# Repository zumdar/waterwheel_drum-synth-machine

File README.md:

# The Wacky Waterwheel Wonder Machine!

A synthesizer, drum machine, electromechanical, waterwheel powered musical intsrument!

.jpg>)

Started in Oct. 2022 in Nashville, TN as part of The Paradise Driveway residency, full working version complete in Oct. 2025.

Project created in collaboration with

- [Neil Fridd (aka Terror Pigeon)](https://terrorpigeon.bandcamp.com/)
- [Jen Gavin (aka Paradise MIDI)](https://paradisemidi.com/)

# Overview

The Waterwheel Wondermachine is a nature powered mechanical-electronic logic idea workstation. It is a hybrid of bass synthesizer, drum machine, and kinetic motor instrument. When it rains, the waterwheel spins and every spoke of the wheel triggers the machine to advance one step of the sequence.

It has the feel of an old analog switch board or the cockpit of an airplane with 50+ toggle switches, patch cables, and LEDs scattered everywhere. Intimidating as it may look from the outside — and even more so on the inside since the front panels are translucent — the machine is simple enough where anyone can walk up and play it!

When it rains, the machine generates evolving musical sequences mixed with the percussive sounds of the external motors striking parts of the frame. When the sun returns, it transforms into a contemplative sound sculpture, droning notes played on the touch canvas panel.

You can play a melody on the waterwheel drawing, using its cleverly arranged key sequence to inspire a new variation on the original idea. All of this is contingent on the correct environmental conditions (rain), so that you have a consistent performance. The rain sounds also play a sonic role, incorporating into the spacial ambiance.

# Tech Specs

- 16 step bass synthesizer sequencer
- 8 step, 4 sample drum sequencer
- 2x motor outputs, motors mounted in the instrument area, creating sounds by clever mounting with the motors hitting parts of the frame.
- All timing and sequencing done with CD4xxx logic chips and digital circuity, a complex puzzle of logic chips, inputs and outputs and buffering.
- the note input of the synthesizer is a drawing of a waterwheel and tree house (homage to Neil s backyard). We cut these pieces out of metal and are using capacitive touch to send those notes to the synthesizer.
- 1 big sample button to trigger a sample whenever the performer wants

# PCB

## V1 - etched

- Schematic was designed in October 2022. A PCB (well 3 actually...) were designed and then etched on the driveway on copper clad FR4 board. Here is the design:

- The etched PCB was tested and then a full PCB was designed and fabricated by JLCPCB

## V2 - fabricated PCB

[Link to Schematic for V2](https://github.com/zumdar/waterwheel_drum-synth-machine/blob/main/PCB/pcb_files_v2%20-%20fabricated%20PCB/waterwhel_V2_SCHEMATIC.pdf)

## PCB V2 errors

- no pulldown for clock
- 555 footprint doesnt fit
- some silkscreen labels are covered up by connectors

# References

[getting trigger from sequencer - casper electronics ](https://web.archive.org/web/20130509102109/http://casperelectronics.com/2007/03/19/sequencer-update/)

[more info about multi channel 4017 sequencer/trigger - sailor mouth](https://web.archive.org/web/20160915053601/http://www.sailormouth.org/trigseq2.html)

[how to get a easy trigger with the 4017 sequecner - little gate seq - electro music forum](https://electro-music.com/forum/topic-63020.html)

[MFOS 4017 sequencer lots of good info on how it works](http://musicfromouterspace.com/analogsynth_new/TENSTEPSEQUENCER/TENSTEPSEQUENCER.php)

[classic baby 10 sequencer](https://hackaday.com/2016/01/14/oh-baby-baby10-build-a-classic-analog-music-sequencer/)

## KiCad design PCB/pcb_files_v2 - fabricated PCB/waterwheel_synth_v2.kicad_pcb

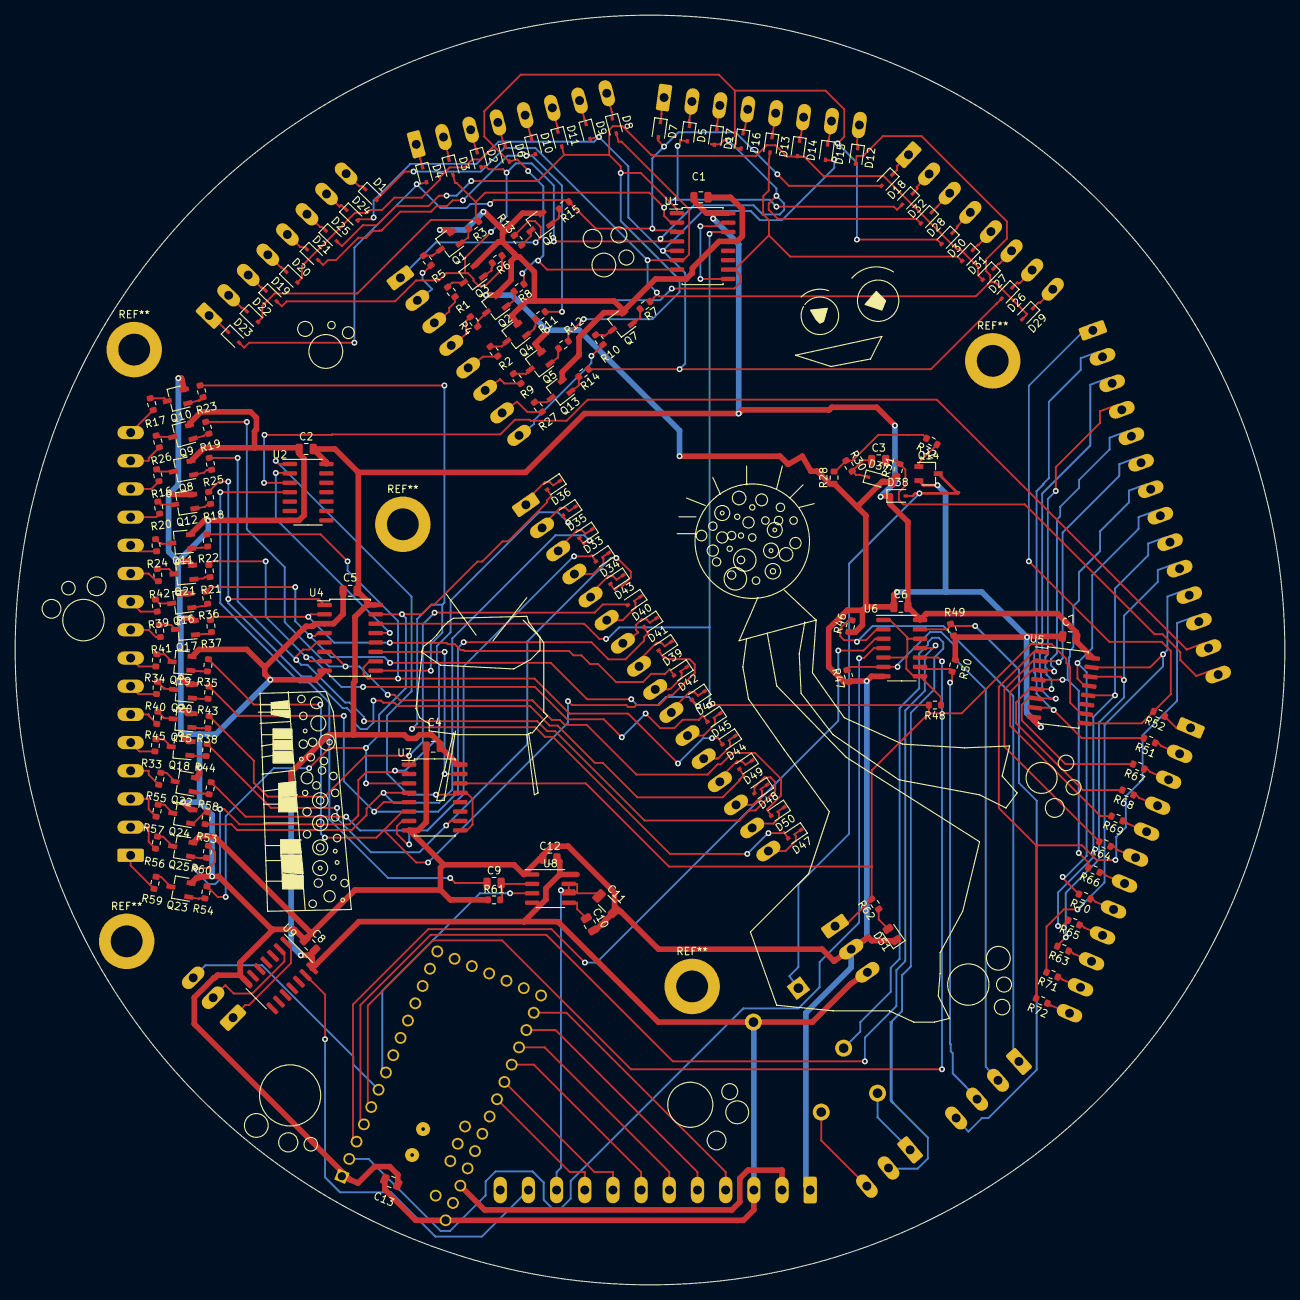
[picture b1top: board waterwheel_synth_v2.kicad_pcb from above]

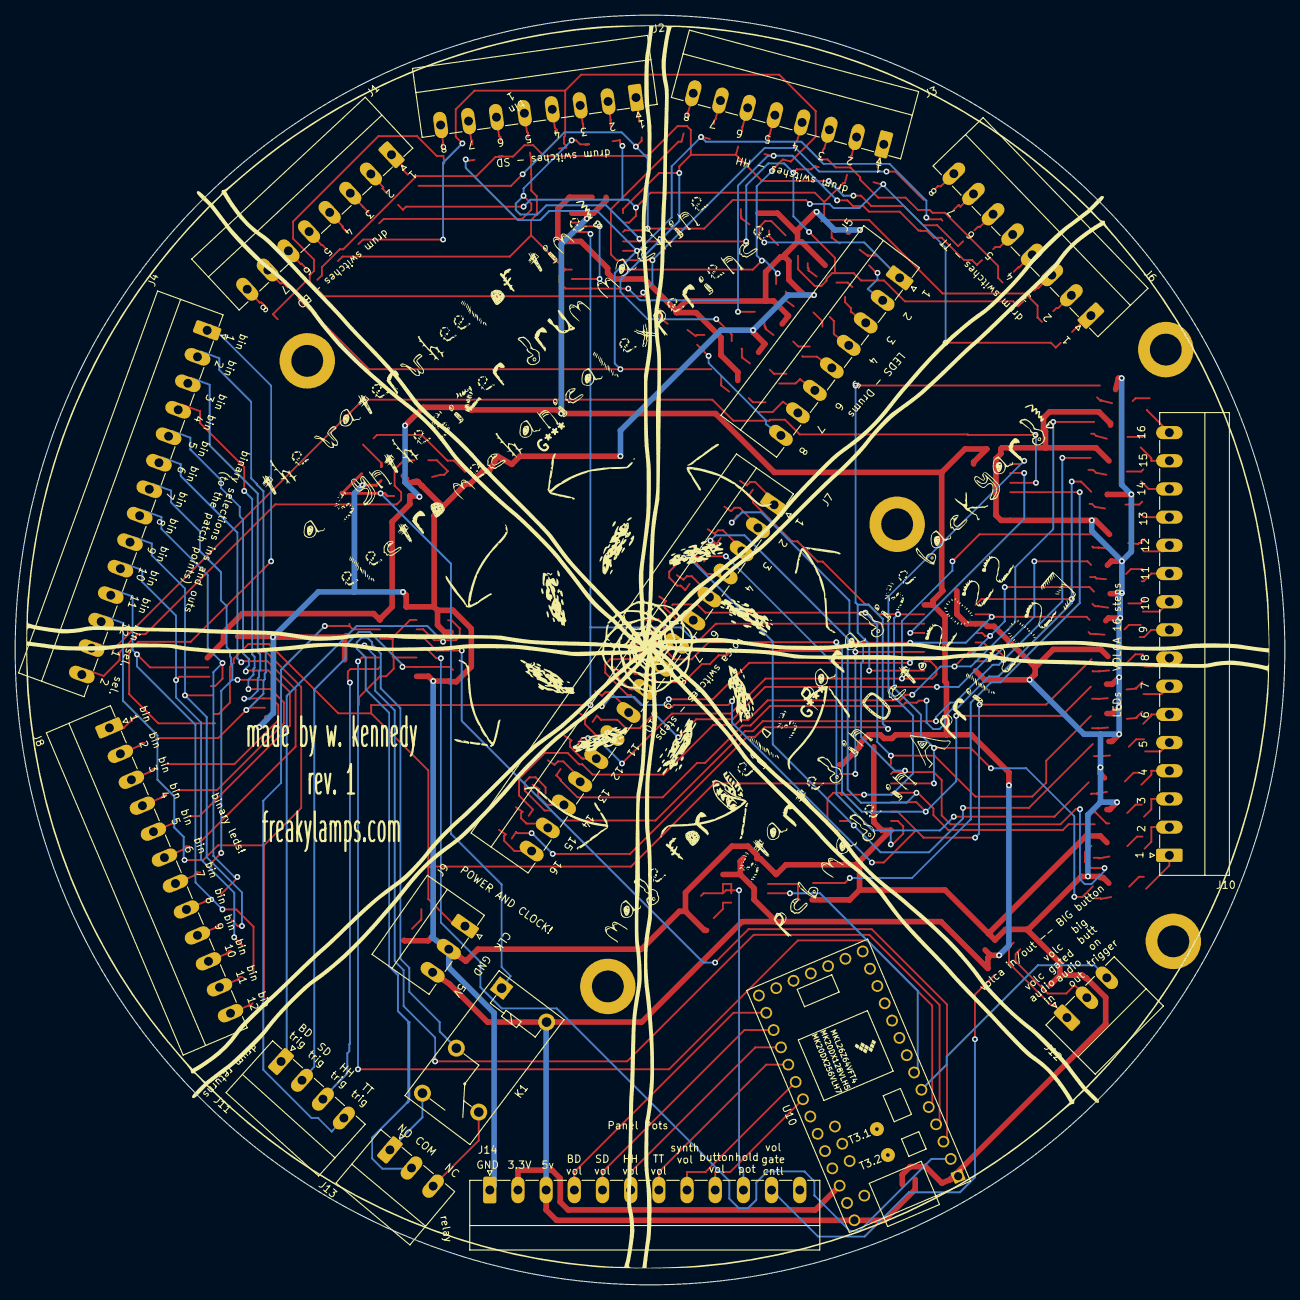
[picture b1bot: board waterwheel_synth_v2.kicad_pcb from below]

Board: 2 copper layers, 171.7 x 171.7 mm, 184 parts (16 on the bottom side), 210 nets.

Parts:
C1, C2, C4, C5, C6, C7, C8: 100nf; C_0805_2012Metric
C3, C9: 4.7u; C_0805_2012Metric
C10, C13: 0.1u; C_0805_2012Metric
C11: 100u; C_1206_3216Metric
C12: 2.2u; C_0805_2012Metric
D1, D2, D3, D4, D5, D6, D7, D8, D9, D10, D11, D12, D13, D14, D15, D16, D17, D18, D19, D20, D21, D22, D23, D24, D25, D26, D27, D28, D29, D30, D31, D32, D33, D34, D35, D36, D37, D38, D39, D40, D41, D42, D43, D44, D45, D46, D47, D48, D49, D50: 1N4148; D_SOD-323
D51: LED; D_0805_2012Metric
J1: Drum_SW_BD; PhoenixContact_MC_1,5_8-G-3.81_1x08_P3.81mm_Horizontal
J2: Drum_SW_SD; PhoenixContact_MC_1,5_8-G-3.81_1x08_P3.81mm_Horizontal
J3: Drum_sw_HH; PhoenixContact_MC_1,5_8-G-3.81_1x08_P3.81mm_Horizontal
J4: 12x binary outs, 2x ins; PhoenixContact_MC_1,5_14-G-3.81_1x14_P3.81mm_Horizontal
J5: LED_drums; PhoenixContact_MC_1,5_8-G-3.81_1x08_P3.81mm_Horizontal
J6: Drum_sw_TT; PhoenixContact_MC_1,5_8-G-3.81_1x08_P3.81mm_Horizontal
J7: Volca_steps; PhoenixContact_MC_1,5_16-G-3.81_1x16_P3.81mm_Horizontal
J8: LED_binary; PhoenixContact_MC_1,5_12-G-3.81_1x12_P3.81mm_Horizontal
J9: power and clock; PhoenixContact_MC_1,5_3-G-3.81_1x03_P3.81mm_Horizontal
J10: LEDS_volca; PhoenixContact_MC_1,5_16-G-3.81_1x16_P3.81mm_Horizontal
J11: Drum_Returns; PhoenixContact_MC_1,5_4-G-3.81_1x04_P3.81mm_Horizontal
J12: volc audio in/out. button trig; PhoenixContact_MC_1,5_3-G-3.81_1x03_P3.81mm_Horizontal
J13: RELAY out; PhoenixContact_MC_1,5_3-G-3.81_1x03_P3.81mm_Horizontal
J14: panel pots; PhoenixContact_MC_1,5_12-G-3.81_1x12_P3.81mm_Horizontal
K1: G5Q-1; Relay_SPDT_Omron-G5Q-1
Q1, Q2, Q3, Q4, Q5, Q6, Q7, Q8, Q9, Q10, Q11, Q12, Q13, Q14, Q15, Q16, Q17, Q18, Q19, Q20, Q21, Q22, Q23, Q24, Q25: 2N3904; TSOT-23
R1, R2, R4, R5, R9, R10, R13, R16, R17, R20, R24, R26, R27, R32, R33, R34, R39, R40, R41, R42, R45, R55, R56, R57, R59, R62: 1k; R_0603_1608Metric
R3, R6, R7, R8, R11, R12, R14, R15, R18, R19, R21, R22, R23, R25, R35, R36, R37, R38, R43, R44, R53, R54, R58, R60: 100k; R_0603_1608Metric
R28, R30, R31: 22k; R_0603_1608Metric
R46, R47, R49, R50, R61: 10k; R_0603_1608Metric
R48: 4.7k; R_0603_1608Metric
R51, R52, R63, R64, R65, R66, R67, R68, R69, R70, R71, R72: 470; R_0603_1608Metric
U1, U4, U7: 4017; SO-16_5.3x10.2mm_P1.27mm
U2: 4069; SO-14_3.9x8.65mm_P1.27mm
U5: 4040; SO-16_5.3x10.2mm_P1.27mm
U6: 4081; SO-14_3.9x8.65mm_P1.27mm
U8: 555(NEW_layout); SOIC-8_3.9x4.9mm_P1.27mm
U9: 4066; SO-14_3.9x8.65mm_P1.27mm
U10: Teensy3.2; Teensy30_31_32_LC

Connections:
1_1: D4.2 (A), D7.2 (A), D18.2 (A), D23.2 (A), R15.1, U1.3 (Q0)
1_2: D3.2 (A), D5.2 (A), D22.2 (A), D32.2 (A), R3.1, U1.2 (Q1)
1_3: D2.2 (A), D17.2 (A), D19.2 (A), D28.2 (A), R6.1, U1.4 (Q2)
1_4: D6.2 (A), D16.2 (A), D20.2 (A), D30.2 (A), R8.1, U1.7 (Q3)
1_5: D10.2 (A), D13.2 (A), D21.2 (A), D31.2 (A), R11.1, U1.10 (Q4)
1_6: D11.2 (A), D14.2 (A), D25.2 (A), D27.2 (A), R12.1, U1.1 (Q5)
1_7: D9.2 (A), D15.2 (A), D24.2 (A), D26.2 (A), R14.1, U1.5 (Q6)
1_8: D1.2 (A), D8.2 (A), D12.2 (A), D29.2 (A), R7.1, U1.6 (Q7)
2_1: D36.2 (A), R54.1, U4.15 (Reset), U7.3 (Q0)
2_2: D35.2 (A), R60.1, U7.2 (Q1)
2_3: D33.2 (A), R53.1, U7.4 (Q2)
2_4: D34.2 (A), R58.1, U7.7 (Q3)
2_5: D43.2 (A), R44.1, U7.10 (Q4)
2_6: D40.2 (A), R38.1, U7.1 (Q5)
2_7: D41.2 (A), R43.1, U7.5 (Q6)
2_8: D39.2 (A), R35.1, U7.6 (Q7)
2_9: D42.2 (A), R37.1, U4.2 (Q1)
2_10: D46.2 (A), R36.1, U4.4 (Q2)
2_11: D45.2 (A), R21.1, U4.7 (Q3)
2_12: D44.2 (A), R22.1, U4.10 (Q4)
2_13: D49.2 (A), R18.1, U4.1 (Q5)
2_14: D48.2 (A), R25.1, U4.5 (Q6)
2_15: D50.2 (A), R19.1, U4.6 (Q7)
2_16: D47.2 (A), R23.1, U4.9 (Q8)
+3V3: J14.2, U10.31 (3.3V)
+5V: C1.2, C2.2, C4.2, C5.2, C6.2, C7.2, C8.2, C12.2, C13.2, D38.1 (K), J9.3, J14.3, K1.5, U1.16 (VDD), U2.14 (VDD), U4.16 (VDD), U5.16 (VDD), U6.14 (VDD), U7.16 (VDD), U8.4 (R), U8.8 (VCC), U9.14 (VDD), U10.33 (Vin)
A_1: D18.1 (K), J1.1
A_2: D32.1 (K), J1.2
A_3: D28.1 (K), J1.3
A_4: D30.1 (K), J1.4
A_5: D31.1 (K), J1.5
A_6: D27.1 (K), J1.6
A_7: D26.1 (K), J1.7
A_8: D29.1 (K), J1.8
BD_Trig_long: J11.1, R46.2, U6.2
BD_Trig_short: U6.3, U10.3 (1_TX1_Touch)
BD_vol: J14.4, U10.21 (14_A0_SCK)
BINARY_1: J4.1, R52.2, U5.9 (Q0)
BINARY_2: J4.2, R51.2, U5.7 (Q1)
BINARY_3: J4.3, R67.2, U5.6 (Q2)
BINARY_4: J4.4, R68.2, U5.5 (Q3)
BINARY_5: J4.5, R69.2, U5.3 (Q4)
BINARY_6: J4.6, R64.2, U5.2 (Q5)
BINARY_7: J4.7, R66.2, U5.4 (Q6)
BINARY_8: J4.8, R70.2, U5.13 (Q7)
BINARY_9: J4.9, R65.2, U5.12 (Q8)
BINARY_10: J4.10, R63.2, U5.14 (Q9)
BINARY_11: J4.11, R71.2, U5.15 (Q10)
BINARY_12: J4.12, R72.2, U5.1 (Q11)
B_1: D7.1 (K), J2.1
B_2: D5.1 (K), J2.2
B_3: D17.1 (K), J2.3
B_4: D16.1 (K), J2.4
B_5: D13.1 (K), J2.5
B_6: D14.1 (K), J2.6
B_7: D15.1 (K), J2.7
B_8: D12.1 (K), J2.8
C_1: D4.1 (K), J3.1
C_2: D3.1 (K), J3.2
C_3: D2.1 (K), J3.3
C_4: D6.1 (K), J3.4
C_5: D10.1 (K), J3.5
C_6: D11.1 (K), J3.6
C_7: D9.1 (K), J3.7
C_8: D8.1 (K), J3.8
D_1: D23.1 (K), J6.1
D_2: D22.1 (K), J6.2
D_3: D19.1 (K), J6.3
D_4: D20.1 (K), J6.4
D_5: D21.1 (K), J6.5
D_6: D25.1 (K), J6.6
D_7: D24.1 (K), J6.7
D_8: D1.1 (K), J6.8
GND: C1.1, C2.1, C4.1, C5.1, C6.1, C7.1, C8.1, C10.2, C11.2, C12.1, C13.1, D37.2 (A), D51.1 (K), J9.2, J14.1, Q1.2 (E), Q2.2 (E), Q3.2 (E), Q4.2 (E), Q5.2 (E), Q6.2 (E), Q7.2 (E), Q8.2 (E), Q9.2 (E), Q10.2 (E), Q11.2 (E), Q12.2 (E), Q13.2 (E), Q14.2 (E), Q15.2 (E), Q16.2 (E), Q17.2 (E), Q18.2 (E), Q19.2 (E), Q20.2 (E), Q21.2 (E), Q22.2 (E), Q23.2 (E), Q24.2 (E), Q25.2 (E), R28.1, R31.1, R46.1, R47.1, R49.1, R50.1, R61.1, U1.8 (VSS), U1.13 (CKEN), U2.7 (VSS), U4.3 (Q0), U4.8 (VSS), U5.8 (VSS), U6.7 (VSS), U7.8 (VSS), U8.1 (GND), U9.7 (VSS), U10.1 (GND)
HH_Trig_long: J11.3, R50.2, U6.9
HH_Trig_short: U6.10, U10.5 (3_TX_PWM)
HH_vol: J14.6, U10.23 (16_A2_SCL0_Touch)
LED1_1: J5.1, R13.2
LED1_2: J5.2, R5.2
LED1_3: J5.3, R1.2
LED1_4: J5.4, R4.2
LED1_5: J5.5, R2.2
LED1_6: J5.6, R9.2
LED1_7: J5.7, R27.2
LED1_8: J5.8, R10.2
LED2_1: J10.1, R59.2
LED2_2: J10.2, R56.2
LED2_3: J10.3, R57.2
LED2_4: J10.4, R55.2
LED2_5: J10.5, R33.2
LED2_6: J10.6, R45.2
LED2_7: J10.7, R40.2
LED2_8: J10.8, R34.2
LED2_9: J10.9, R41.2
LED2_10: J10.10, R39.2
LED2_11: J10.11, R42.2
LED2_12: J10.12, R24.2
LED2_13: J10.13, R20.2
LED2_14: J10.14, R16.2
LED2_15: J10.15, R26.2
LED2_16: J10.16, R17.2
LED_BIN_1: J8.1, R52.1
LED_BIN_2: J8.2, R51.1
LED_BIN_3: J8.3, R67.1
LED_BIN_4: J8.4, R68.1
LED_BIN_5: J8.5, R69.1
LED_BIN_6: J8.6, R64.1
LED_BIN_7: J8.7, R66.1
LED_BIN_8: J8.8, R70.1
LED_BIN_9: J8.9, R65.1
LED_BIN_10: J8.10, R63.1
LED_BIN_11: J8.11, R71.1
LED_BIN_12: J8.12, R72.1
unnamed: C3.1, D37.1 (K), R30.2
unnamed: C9.2, R61.2, U8.2 (TR)
unnamed: C10.1, U8.5 (CV)
unnamed: D38.2 (A), K1.1, Q14.3 (C)
unnamed: D51.2 (A), R62.1
unnamed: Q1.1 (B), R3.2
unnamed: Q1.3 (C), R5.1
unnamed: Q2.1 (B), R8.2
unnamed: Q2.3 (C), R4.1
unnamed: Q3.1 (B), R6.2
unnamed: Q3.3 (C), R1.1
unnamed: Q4.1 (B), R11.2
unnamed: Q4.3 (C), R2.1
unnamed: Q5.1 (B), R12.2
unnamed: Q5.3 (C), R9.1
unnamed: Q6.1 (B), R15.2
unnamed: Q6.3 (C), R13.1
unnamed: Q7.1 (B), R7.2
unnamed: Q7.3 (C), R10.1
unnamed: Q8.1 (B), R25.2
unnamed: Q8.3 (C), R16.1
unnamed: Q9.1 (B), R19.2
unnamed: Q9.3 (C), R26.1
unnamed: Q10.1 (B), R23.2
unnamed: Q10.3 (C), R17.1
unnamed: Q11.1 (B), R22.2
unnamed: Q11.3 (C), R24.1
unnamed: Q12.1 (B), R18.2
unnamed: Q12.3 (C), R20.1
unnamed: Q13.1 (B), R14.2
unnamed: Q13.3 (C), R27.1
unnamed: Q14.1 (B), R32.1
unnamed: Q15.1 (B), R38.2
unnamed: Q15.3 (C), R45.1
unnamed: Q16.1 (B), R36.2
unnamed: Q16.3 (C), R39.1
unnamed: Q17.1 (B), R37.2
unnamed: Q17.3 (C), R41.1
unnamed: Q18.1 (B), R44.2
unnamed: Q18.3 (C), R33.1
unnamed: Q19.1 (B), R35.2
unnamed: Q19.3 (C), R34.1
unnamed: Q20.1 (B), R43.2
unnamed: Q20.3 (C), R40.1
unnamed: Q21.1 (B), R21.2
unnamed: Q21.3 (C), R42.1
unnamed: Q22.1 (B), R58.2
unnamed: Q22.3 (C), R55.1
unnamed: Q23.1 (B), R54.2
unnamed: Q23.3 (C), R59.1
unnamed: Q24.1 (B), R53.2
unnamed: Q24.3 (C), R57.1
unnamed: Q25.1 (B), R60.2
unnamed: Q25.3 (C), R56.1
unnamed: R28.2, R30.1, R32.2
unnamed: R48.1, U6.1, U6.5, U6.8, U6.12
unnamed: U1.9 (Q8), U1.15 (Reset)
unnamed: U2.1, U7.9 (Q8), U7.13 (CKEN)
unnamed: U2.2, U4.13 (CKEN)
unnamed: U4.11 (Q9), U7.15 (Reset)
SD_trig_long: J11.2, R47.2, U6.6
SD_trig_short: U6.4, U10.2 (0_RX1_Touch)
SD_vol: J14.5, U10.22 (15_A1_CS_Touch)
TT_Trig_long: J11.4, R49.2, U6.13
TT_Trig_short: U6.11, U10.4 (2)
TT_vol: J14.7, U10.24 (17_A3_SDA0_Touch)
Volca_step_1: D36.1 (K), J7.1
Volca_step_2: D35.1 (K), J7.2
Volca_step_3: D33.1 (K), J7.3
Volca_step_4: D34.1 (K), J7.4
Volca_step_5: D43.1 (K), J7.5
Volca_step_6: D40.1 (K), J7.6
Volca_step_7: D41.1 (K), J7.7
Volca_step_8: D39.1 (K), J7.8
Volca_step_9: D42.1 (K), J7.9
Volca_step_10: D46.1 (K), J7.10
Volca_step_11: D45.1 (K), J7.11
Volca_step_12: D44.1 (K), J7.12
Volca_step_13: D49.1 (K), J7.13
Volca_step_14: D48.1 (K), J7.14
Volca_step_15: D50.1 (K), J7.15
Volca_step_16: D47.1 (K), J7.16
ambient_trigger_to_teensy: U8.3 (Q), U10.7 (5_TX1_PWM)
big_button_sound_vol: J14.9, U10.26 (19_A5_SCL0_Touch)
big_button_trig: J12.3, U10.6 (4_RX_PWM)
clock: J9.1, R48.2, R62.2, U1.14 (CLK), U4.14 (CLK), U5.10 (CLK), U7.14 (CLK)
hold_pot: C11.1, J14.10, U8.6 (THR), U8.7 (DIS)
relay-NC: J13.3, K1.4
relay-NO: J13.1, K1.3
relay-com: J13.2, K1.2
sel_trig_inv: C9.1, U2.4
selected_trig: J4.13, U2.3
selected_trig2: C3.2, J4.14, R31.2
synth_vol: J14.8, U10.25 (18_A4_SDA0_Touch)
volca_audio: J12.1, U9.1
volca_audio_gated: J12.2, U9.2
volca_gate_control: J14.11, U9.13

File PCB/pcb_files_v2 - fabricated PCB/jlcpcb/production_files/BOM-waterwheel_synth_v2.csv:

Comment,Designator,Footprint,LCSC
100u,C11,C_1206_3216Metric,C15008
1k,"R1,R10,R13,R16,R17,R2,R20,R24,R26,R27,R32,R33,R34,R39,R4,R40,R41,R42,R45,R5,R55,R56,R57,R59,R62,R9",R_0603_1608Metric,C17513
4.7u,"C3,C9",C_0805_2012Metric,C1779
4069,U2,SO-14_3.9x8.65mm_P1.27mm,C194330
1N4148,"D1,D10,D11,D12,D13,D14,D15,D16,D17,D18,D19,D2,D20,D21,D22,D23,D24,D25,D26,D27,D28,D29,D3,D30,D31,D32,D33,D34,D35,D36,D37,D38,D39,D4,D40,D41,D42,D43,D44,D45,D46,D47,D48,D49,D5,D50,D6,D7,D8,D9",D_SOD-323,C2128
2N3904,"Q1,Q10,Q11,Q12,Q13,Q14,Q15,Q16,Q17,Q18,Q19,Q2,Q20,Q21,Q22,Q23,Q24,Q25,Q3,Q4,Q5,Q6,Q7,Q8,Q9",TSOT-23,C2146
4.7k,R48,R_0603_1608Metric,C23162
470,"R51,R52,R63,R64,R65,R66,R67,R68,R69,R70,R71,R72",R_0603_1608Metric,C23179
100k,"R11,R12,R14,R15,R18,R19,R21,R22,R23,R25,R3,R35,R36,R37,R38,R43,R44,R53,R54,R58,R6,R60,R7,R8",R_0603_1608Metric,C25803
10k,"R46,R47,R49,R50,R61",R_0603_1608Metric,C25804
100nf,"C1,C2,C4,C5,C6,C7,C8",C_0805_2012Metric,C28233
22k,"R28,R30,R31",R_0603_1608Metric,C31850
4040,U5,SO-16_5.3x10.2mm_P1.27mm,C353974
4017,"U1,U4,U7",SO-16_5.3x10.2mm_P1.27mm,C356694
4081,U6,SO-14_3.9x8.65mm_P1.27mm,C40551
2.2u,C12,C_0805_2012Metric,C49217
0.1u,"C10,C13",C_0805_2012Metric,C49678
4066,U9,SO-14_3.9x8.65mm_P1.27mm,C54755
555(NEW_layout),U8,SOIC-8_5.275x5.275mm_P1.27mm,C7593
LED,D51,D_0805_2012Metric,C84256
RELAY out,J13,"PhoenixContact_MC_1,5_3-G-3.81_1x03_P3.81mm_Horizontal",
volc audio in/out. button trig,J12,"PhoenixContact_MC_1,5_3-G-3.81_1x03_P3.81mm_Horizontal",
Drum_Returns,J11,"PhoenixContact_MC_1,5_4-G-3.81_1x04_P3.81mm_Horizontal",
LEDS_volca,J10,"PhoenixContact_MC_1,5_16-G-3.81_1x16_P3.81mm_Horizontal",
power and clock,J9,"PhoenixContact_MC_1,5_3-G-3.81_1x03_P3.81mm_Horizontal",
LED_binary,J8,"PhoenixContact_MC_1,5_12-G-3.81_1x12_P3.81mm_Horizontal",
Volca_steps,J7,"PhoenixContact_MC_1,5_16-G-3.81_1x16_P3.81mm_Horizontal",
Drum_sw_TT,J6,"PhoenixContact_MC_1,5_8-G-3.81_1x08_P3.81mm_Horizontal",
LED_drums,J5,"PhoenixContact_MC_1,5_8-G-3.81_1x08_P3.81mm_Horizontal",
"12x binary outs, 2x ins",J4,"PhoenixContact_MC_1,5_14-G-3.81_1x14_P3.81mm_Horizontal",
Drum_sw_HH,J3,"PhoenixContact_MC_1,5_8-G-3.81_1x08_P3.81mm_Horizontal",
Drum_SW_SD,J2,"PhoenixContact_MC_1,5_8-G-3.81_1x08_P3.81mm_Horizontal",
Drum_SW_BD,J1,"PhoenixContact_MC_1,5_8-G-3.81_1x08_P3.81mm_Horizontal",
Teensy3.2,U10,Teensy30_31_32_LC,
G5Q-1,K1,Relay_SPDT_Omron-G5Q-1,
panel pots,J14,"PhoenixContact_MC_1,5_12-G-3.81_1x12_P3.81mm_Horizontal",

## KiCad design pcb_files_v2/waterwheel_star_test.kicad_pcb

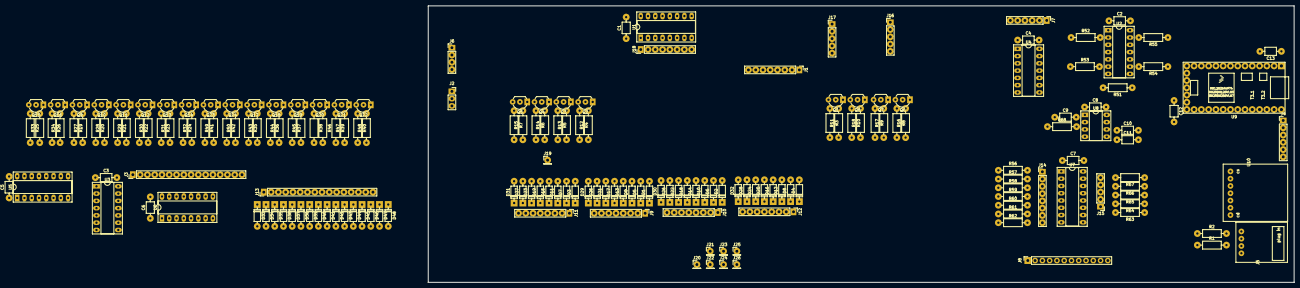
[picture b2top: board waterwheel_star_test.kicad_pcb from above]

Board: 2 copper layers, 302.3 x 96.5 mm, 189 parts (0 on the bottom side), 212 nets, no tracks yet.

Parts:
C1, C2, C3, C4, C5, C6, C7: 100nf; C_Axial_L3.8mm_D2.6mm_P7.50mm_Horizontal_BIG
C8: 2.2u; C_Axial_L3.8mm_D2.6mm_P7.50mm_Horizontal_BIG
C9, C12: 4.7u; C_Axial_L3.8mm_D2.6mm_P7.50mm_Horizontal_BIG
C10: 100u; C_Axial_L3.8mm_D2.6mm_P7.50mm_Horizontal_BIG
C11, C13: 0.1u; C_Axial_L3.8mm_D2.6mm_P7.50mm_Horizontal_BIG
D1, D2, D3, D4, D5, D6, D7, D8, D9, D10, D11, D12, D13, D14, D15, D16, D17, D18, D19, D20, D21, D22, D23, D24, D25, D26, D27, D28, D29, D30, D31, D32, D33, D34, D35, D36, D37, D38, D39, D40, D41, D42, D43, D44, D45, D46, D47, D48: 1N4148; D_DO-35_SOD27_P7.62mm_Horizontal_BIG
J1, J9, J10, J11, J12, J14: Conn_01x08_Female; PinHeader_1x08_P2.54mm_Vertical_BIG
J2: Conn_01x03_Female; PinSocket_1x03_P2.54mm_Vertical_BIG
J3, J13: Conn_01x16_Female; PinHeader_1x16_P2.54mm_Vertical_BIG
J4, J7: Conn_01x06_Female; PinHeader_1x06_P2.54mm_Vertical_BIG
J5: AudioJack4; sparkfun_headphone_jack
J6: Conn_01x04_Female; PinHeader_1x04_P2.54mm_Vertical_BIG
J8: Conn_01x12_Female; PinSocket_1x12_P2.54mm_Vertical_BIG
J15: Conn_01x05_Female; PinHeader_1x05_P2.54mm_Vertical_BIG
J16: board2_IN; PinHeader_1x05_P2.54mm_Vertical_BIG
J17: board1_OUT; PinHeader_1x05_P2.54mm_Vertical_BIG
J18: 4017_8_out; PinHeader_1x08_P2.54mm_Vertical_BIG
J19, J20, J21, J22, J23, J24, J25, J26: Conn_01x01_Female; PinHeader_1x01_P2.54mm_Vertical_BIG
Q1, Q2, Q3, Q4, Q5, Q6, Q7, Q8, Q9, Q10, Q11, Q12, Q13, Q14, Q15, Q16, Q17, Q18, Q19, Q20, Q21, Q22, Q23, Q24: 2N3904; TO-92_Inline_Wide_BIG
R1, R51: 4.7k; R_Axial_DIN0207_L6.3mm_D2.5mm_P10.16mm_Horizontal_BIG
R2, R3, R4, R5, R6, R7, R8, R9, R10, R19, R20, R21, R22, R23, R24, R25, R26, R35, R36, R37, R38, R39, R40, R41, R42: 1k; R_Axial_DIN0207_L6.3mm_D2.5mm_P10.16mm_Horizontal_BIG
R11, R12, R13, R14, R15, R16, R17, R18, R27, R28, R29, R30, R31, R32, R33, R34, R43, R44, R45, R46, R47, R48, R49, R50: 100k; R_Axial_DIN0207_L6.3mm_D2.5mm_P10.16mm_Horizontal_BIG
R52, R53, R54, R55, R68: 10k; R_Axial_DIN0207_L6.3mm_D2.5mm_P10.16mm_Horizontal_BIG
R56, R57, R58, R59, R60, R61, R62, R63, R64, R65, R66, R67: 470; R_Axial_DIN0207_L6.3mm_D2.5mm_P10.16mm_Horizontal_BIG
U1, U5, U6: 4017; DIP-16_W7.62mm_Socket_LongPads
U2: 4081; DIP-14_W7.62mm_Socket_LongPads
U3: 4069; DIP-14_W7.62mm_Socket_LongPads
U4: 4066; DIP-14_W7.62mm_Socket_LongPads
U7: 4040; DIP-16_W7.62mm_Socket_LongPads
U8: 555(NEW_layout); DIP-8_W7.62mm_Socket_LongPads
U9: Teensy3.2; Teensy30_31_32_LC_BIG
U10: micro_sd; sparkfun_sd_card

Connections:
1_1: D1.2, D2.2, D3.2, D4.2, J19.1, R16.1
1_2: D5.2, D6.2, D7.2, D8.2, J20.1, R17.1
1_3: D9.2, D10.2, D11.2, D12.2, J21.1, R18.1
1_4: D13.2, D14.2, D15.2, D16.2, J22.1, R11.1
1_5: D17.2, D18.2, D19.2, D20.2, J23.1, R12.1
1_6: D21.2, D22.2, D23.2, D24.2, J24.1, R13.1
1_7: D25.2, D26.2, D27.2, D28.2, J25.1, R14.1
1_8: D29.2, D30.2, D31.2, D32.2, J26.1, R15.1
2_1: D33.2, R33.1, U5.3, U6.15
2_2: D34.2, R34.1, U5.2
2_3: D35.2, R27.1, U5.4
2_4: D36.2, R28.1, U5.7
2_5: D37.2, R29.1, U5.10
2_6: D38.2, R30.1, U5.1
2_7: D39.2, R31.1, U5.5
2_8: D40.2, R32.1, U5.6
2_9: D41.2, R49.1, U6.2
2_10: D42.2, R50.1, U6.4
2_11: D43.2, R43.1, U6.7
2_12: D44.2, R44.1, U6.10
2_13: D45.2, R45.1, U6.1
2_14: D46.2, R46.1, U6.5
2_15: D47.2, R47.1, U6.6
2_16: D48.2, R48.1, U6.9
+3V3: J4.5, U9.31
+5V: C1.2, C2.2, C3.2, C4.2, C5.2, C6.2, C7.2, C8.2, C13.2, J4.4, J6.1, J6.2, J16.1, J17.1, U1.16, U2.14, U3.14, U4.14, U5.16, U6.16, U7.16, U8.4, U8.8, U9.33, U10.5
BD_Trig_long: J7.1, R52.2, U2.2
BD_Trig_short: U2.3, U9.2
CS: U9.10, U10.7
DIN: U9.14, U10.2
DOUT: U9.13, U10.6
GND: C1.1, C2.1, C3.1, C4.1, C5.1, C6.1, C7.1, C8.1, C10.2, C11.2, C13.1, J4.6, J5.S, J6.3, J6.4, J16.2, J17.2, Q1.1, Q2.1, Q3.1, Q4.1, Q5.1, Q6.1, Q7.1, Q8.1, Q9.1, Q10.1, Q11.1, Q12.1, Q13.1, Q14.1, Q15.1, Q16.1, Q17.1, Q18.1, Q19.1, Q20.1, Q21.1, Q22.1, Q23.1, Q24.1, R52.1, R53.1, R54.1, R55.1, R68.1, U1.8, U1.13, U2.7, U3.7, U4.7, U5.8, U6.3, U6.8, U7.8, U8.1, U9.1, U10.3
HH_Trig_long: J7.3, R54.2, U2.9
HH_Trig_short: U2.10, U9.4
LED1_1: J1.1, R8.2
LED1_2: J1.2, R9.2
LED1_3: J1.3, R10.2
LED1_4: J1.4, R3.2
LED1_5: J1.5, R4.2
LED1_6: J1.6, R5.2
LED1_7: J1.7, R6.2
LED1_8: J1.8, R7.2
LED2_1: J3.1, R25.2
LED2_2: J3.2, R26.2
LED2_3: J3.3, R19.2
LED2_4: J3.4, R20.2
LED2_5: J3.5, R21.2
LED2_6: J3.6, R22.2
LED2_7: J3.7, R23.2
LED2_8: J3.8, R24.2
LED2_9: J3.9, R41.2
LED2_10: J3.10, R42.2
LED2_11: J3.11, R35.2
LED2_12: J3.12, R36.2
LED2_13: J3.13, R37.2
LED2_14: J3.14, R38.2
LED2_15: J3.15, R39.2
LED2_16: J3.16, R40.2
LED_BIN_1: J8.1, R63.1
LED_BIN_2: J8.2, R62.1
LED_BIN_3: J8.3, R61.1
LED_BIN_4: J8.4, R60.1
LED_BIN_5: J8.5, R58.1
LED_BIN_6: J8.6, R57.1
LED_BIN_7: J8.7, R59.1
LED_BIN_8: J8.8, R65.1
LED_BIN_9: J8.9, R64.1
LED_BIN_10: J8.10, R66.1
LED_BIN_11: J8.11, R67.1
LED_BIN_12: J8.12, R56.1
unnamed: C9.2, R68.2, U8.2
unnamed: C11.1, U8.5
unnamed: C12.1, U9.19
unnamed: D1.1, J9.1
unnamed: D2.1, J10.1
unnamed: D3.1, J11.1
unnamed: D4.1, J12.1
unnamed: D5.1, J9.2
unnamed: D6.1, J10.2
unnamed: D7.1, J11.2
unnamed: D8.1, J12.2
unnamed: D9.1, J9.3
unnamed: D10.1, J10.3
unnamed: D11.1, J11.3
unnamed: D12.1, J12.3
unnamed: D13.1, J9.4
unnamed: D14.1, J10.4
unnamed: D15.1, J11.4
unnamed: D16.1, J12.4
unnamed: D17.1, J9.5
unnamed: D18.1, J10.5
unnamed: D19.1, J11.5
unnamed: D20.1, J12.5
unnamed: D21.1, J9.6
unnamed: D22.1, J10.6
unnamed: D23.1, J11.6
unnamed: D24.1, J12.6
unnamed: D25.1, J9.7
unnamed: D26.1, J10.7
unnamed: D27.1, J11.7
unnamed: D28.1, J12.7
unnamed: D29.1, J9.8
unnamed: D30.1, J10.8
unnamed: D31.1, J11.8
unnamed: D32.1, J12.8
unnamed: D33.1, J13.1
unnamed: D34.1, J13.2
unnamed: D35.1, J13.3
unnamed: D36.1, J13.4
unnamed: D37.1, J13.5
unnamed: D38.1, J13.6
unnamed: D39.1, J13.7
unnamed: D40.1, J13.8
unnamed: D41.1, J13.9
unnamed: D42.1, J13.10
unnamed: D43.1, J13.11
unnamed: D44.1, J13.12
unnamed: D45.1, J13.13
unnamed: D46.1, J13.14
unnamed: D47.1, J13.15
unnamed: D48.1, J13.16
unnamed: J5.R1, J5.R2, R2.2
unnamed: J5.T, R1.2
unnamed: J14.1, R56.2, U7.1
unnamed: J14.2, R57.2, U7.2
unnamed: J14.3, R58.2, U7.3
unnamed: J14.4, R59.2, U7.4
unnamed: J14.5, R60.2, U7.5
unnamed: J14.6, R61.2, U7.6
unnamed: J14.7, R62.2, U7.7
unnamed: J15.1, R63.2, U7.9
unnamed: J15.2, R64.2, U7.12
unnamed: J15.3, R65.2, U7.13
unnamed: J15.4, R66.2, U7.14
unnamed: J15.5, R67.2, U7.15
unnamed: J18.1, U1.1
unnamed: J18.2, U1.2
unnamed: J18.3, U1.3
unnamed: J18.4, U1.4
unnamed: J18.5, U1.5
unnamed: J18.6, U1.6
unnamed: J18.7, U1.7
unnamed: J18.8, U1.10
unnamed: Q1.2, R11.2
unnamed: Q1.3, R3.1
unnamed: Q2.2, R12.2
unnamed: Q2.3, R4.1
unnamed: Q3.2, R13.2
unnamed: Q3.3, R5.1
unnamed: Q4.2, R14.2
unnamed: Q4.3, R6.1
unnamed: Q5.2, R15.2
unnamed: Q5.3, R7.1
unnamed: Q6.2, R16.2
unnamed: Q6.3, R8.1
unnamed: Q7.2, R17.2
unnamed: Q7.3, R9.1
unnamed: Q8.2, R18.2
unnamed: Q8.3, R10.1
unnamed: Q9.2, R27.2
unnamed: Q9.3, R19.1
unnamed: Q10.2, R28.2
unnamed: Q10.3, R20.1
unnamed: Q11.2, R29.2
unnamed: Q11.3, R21.1
unnamed: Q12.2, R30.2
unnamed: Q12.3, R22.1
unnamed: Q13.2, R31.2
unnamed: Q13.3, R23.1
unnamed: Q14.2, R32.2
unnamed: Q14.3, R24.1
unnamed: Q15.2, R33.2
unnamed: Q15.3, R25.1
unnamed: Q16.2, R34.2
unnamed: Q16.3, R26.1
unnamed: Q17.2, R43.2
unnamed: Q17.3, R35.1
unnamed: Q18.2, R44.2
unnamed: Q18.3, R36.1
unnamed: Q19.2, R45.2
unnamed: Q19.3, R37.1
unnamed: Q20.2, R46.2
unnamed: Q20.3, R38.1
unnamed: Q21.2, R47.2
unnamed: Q21.3, R39.1
unnamed: Q22.2, R48.2
unnamed: Q22.3, R40.1
unnamed: Q23.2, R49.2
unnamed: Q23.3, R41.1
unnamed: Q24.2, R50.2
unnamed: Q24.3, R42.1
unnamed: R51.1, U2.1, U2.5, U2.8, U2.12
unnamed: U1.9, U1.15
unnamed: U3.1, U5.9, U5.13
unnamed: U3.2, U6.13
unnamed: U5.15, U6.11
unnamed: U9.20, U10.4
SD_trig_long: J7.2, R53.2, U2.6
SD_trig_short: U2.4, U9.3
TT_Trig_long: J7.4, R55.2, U2.13
TT_Trig_short: U2.11, U9.5
ambient_trigger_to_teensy: U8.3, U9.6
clock: J2.1, J2.2, J2.3, J16.3, J17.3, R51.2, U1.14, U5.14, U6.14, U7.10
drum_vol: J4.2, U9.23
hold_pot: C10.1, J4.1, U8.6, U8.7
sel_trig_inv: C9.1, J16.5, J17.5, U3.4
selected_trig: J14.8, J16.4, J17.4, U3.3
synth_vol: J4.3, U9.24
teensy_audio_out: C12.2, R2.1
volca_audio: J7.6, U4.1
volca_audio_gated: R1.1, U4.2
volca_gate_control: J7.5, U4.13

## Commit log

2023-04-25 first
2023-04-25 readme adding
2023-04-25 updated 555 footprint, it was too big
2023-05-03 adding pdf schematic
2023-05-12 presshow 5.12
2023-05-15 added peters simplified code
2025-10-17 update from oct 2025
2025-10-17 oct 2025 update
2025-11-13 re-organizing folder structure
2025-11-13 updating readme.md
2025-11-13 updating readme and adding pcb images
2025-11-13 small readme changes
